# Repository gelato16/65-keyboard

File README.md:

# 65-keyboard
A 65% keyboard with fully custom parts designed using KiCAD and Solidworks. Made with a resin case, aluminum switch plate and soldered Epomaker silent keyswitches. 
This project is me introduction to Solidworks as someone preparing for a new robotics season, I'm not exactly a keyboard enthusiast (I might be becoming one) so I went with the essential 65% in order to keep things compact. 
features:
- 65% QWERTY layout
- Sandwich style assembly
- 7U spacebar
- Plate-mounted switches
- Custom PCB
- USB-C connection
- Custom switch plate

CAD photos:

PCB photos:

assembly guild: 
this is a sandwich style keyboard, meaning it is assembled in layers into a main base. The pcb slides easily into the main compartment followed by the switch plate, which the key switches click into. the keycaps and bezel finally lay on top and are screwed into place. 
Pictures of assembly design process below: 

Bill of materials:
https://docs.google.com/spreadsheets/d/1lCmeEfUbG34g1hUgpbVch2w63U2JIJnhS8jueZ3TIsw/edit?usp=sharing 
| Id        | Designator                                                                                                              | Footprint                           | Quantity                                                                                      | Designation                   | Link                                                                                          |
| :-------- | :---------------------------------------------------------------------------------------------------------------------- | :---------------------------------- | :-------------------------------------------------------------------------------------------- | :---------------------------- | :-------------------------------------------------------------------------------------------- |
| 1         | MX1-MX69                                                                                                                | SW_MX_HS_CPG151101S11_1u            | 69                                                                                            | MX_SW_HS                      | N/A                                                                                           |
| 2         | U1                                                                                                                      | LQFP-48_7x7mm_P0.5mm                | 1                                                                                             | STM32F072CBT6                 | https://www.digikey.ca/en/products/detail/stmicroelectronics/STM32F072CBT6/4815292            |
| 3         | C1, C3, C4, C5, C6                                                                                                      | C_1206_3126Metric                   | 7                                                                                             | 100nF                         | https://www.digikey.com/en/products/detail/kemet/C1206C104KARACTU/992167                      |
| 4         | C9, C10                                                                                                                 | C_1206_3126Metric                   | 2                                                                                             | 1uF                           | https://www.digikey.ca/en/products/detail/yageo/CC1206KKX7R7BB105/302915                      |
| 5         | R1 - R4                                                                                                                 | R_1206_3126Metric                   | 4                                                                                             | 5.1k                          | https://www.digikey.com/en/products/detail/stackpole-electronics-inc/RMCF1206FT5K10/1759499   |
| 6         | BOOT1, RST1                                                                                                             | SW_SPST_TL3342                      | 2                                                                                             | SW_SPST                       | https://jlcpcb.com/partdetail/ESwitch-TL3342F260QG/C2886894                                   |
| 7         | J1                                                                                                                      | USB_C_Receptacle_HRO_TYPE-C-31-M-12 | 1                                                                                             | USB_C_Receptacle_USB2.0       | https://jlcpcb.com/partdetail/C9900015525                                                     |
| 8         | F1                                                                                                                      | Fuse_1206_3216Metric                | 1                                                                                             | 500mA                         | https://www.lcsc.com/product-detail/C135341.html                                              |
| 9         | U5                                                                                                                      | C_0402_1005Metric                   | 1                                                                                             | TXB0101                       | https://www.lcsc.com/product-detail/C324081.html                                              |
| 10        | U3                                                                                                                      | SOT-23                              | 1                                                                                             | XC6206PxxxMR-Regulator_Linear | https://www.lcsc.com/product-detail/C5446.html                                                |
| 11        | D1-D69                                                                                                                  | D_SOD-123                           | 69                                                                                            | D_small                       | https://www.digikey.ca/en/products/detail/shenzhen-slkormicro-semicon-co-ltd/1N4148W/21853071 |
| 12        | U2                                                                                                                      | SOT-143                             | 1                                                                                             | PRTR5V0U2X                    | https://www.digikey.ca/en/products/detail/nexperia-usa-inc/PRTR5V0U2X-215/1163690             |
| 13        | C2                                                                                                                      | C_1206_3216Metric                   | 1                                                                                             | 10uF                          | https://www.digikey.ca/en/products/detail/kemet/C1206C106K8RACTU/1090842                      |
| 14        | C43, C44                                                                                                                | C_1206_3216Metric                   | 2                                                                                             | 0.1uF                         | https://www.digikey.ca/en/products/detail/tdk/C3216X7R2A104M160AA/513969                      |
| 15        | J2                                                                                                                      | PinHeader_1x05_P2.54mm_Vertical     | 1                                                                                             | Conn_01x05                    | https://www.digikey.ca/en/products/detail/harwin-inc/M20-9990546/3728232                      |
| 16        | J3                                                                                                                      | PinHeader_1x06_P2.54mm_Vertical     | 1                                                                                             | Conn_01x06                    | https://www.digikey.ca/en/products/detail/sullins-connector-solutions/PEC06SAFN/859339        |
|           |                                                                                                                         |                                     |                                                                                               |                               |                                                                                               |
| Physical: |                                                                                                                         |                                     |                                                                                               |                               |                                                                                               |
| Id        | Name                                                                                                                    | quantity                            | link                                                                                          |                               |                                                                                               |
| 1         | EPOMAKER Roseveil Silent Switch Set                                                                                     | 1                                   | https://epomaker.ca/products/epomaker-roseveil-silent-switch-set?_pos=3&_sid=4f9293093&_ss=r  |                               |                                                                                               |
| 2         | DUROCK Plate Mount Stabilizer V3                                                                                        | 1                                   | https://www.amazon.ca/dp/B0CTHT34MJ?ref=ppx_yo2ov_dt_b_fed_asin_title&th=1                    |                               |                                                                                               |
| 3         | dagaladoo Coffee Cat 140key keycaps,XDA Profile,dye Sublimation PBT Custom keycap with Key Puller for Gateron MX Switch | 1                                   | https://www.amazon.ca/dp/B0CF1ZS6D4?ref=ppx_yo2ov_dt_b_fed_asin_title&th=1                    |                               |                                                                                               |

All designs complete, assembly ongoing
(designed using Kicad, Solidworks and sketchbook)
(files with numbers ex:open2, are completed(not verified works.)

Known issues: None, 
Credits: My father for introducing me to all this. 
Sanity checked by my lovely best friend & my tech teacher

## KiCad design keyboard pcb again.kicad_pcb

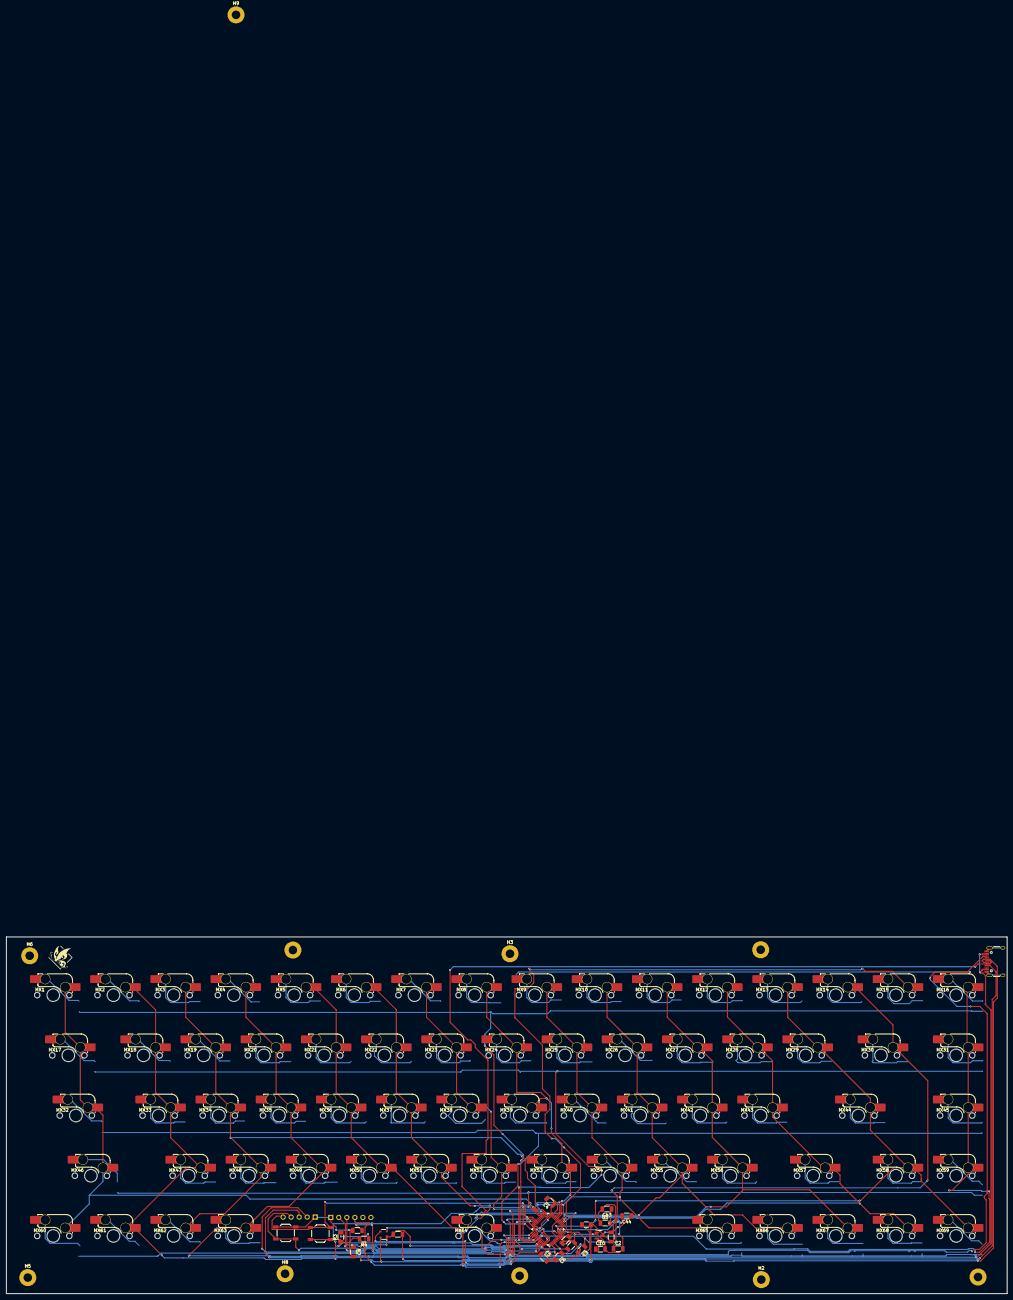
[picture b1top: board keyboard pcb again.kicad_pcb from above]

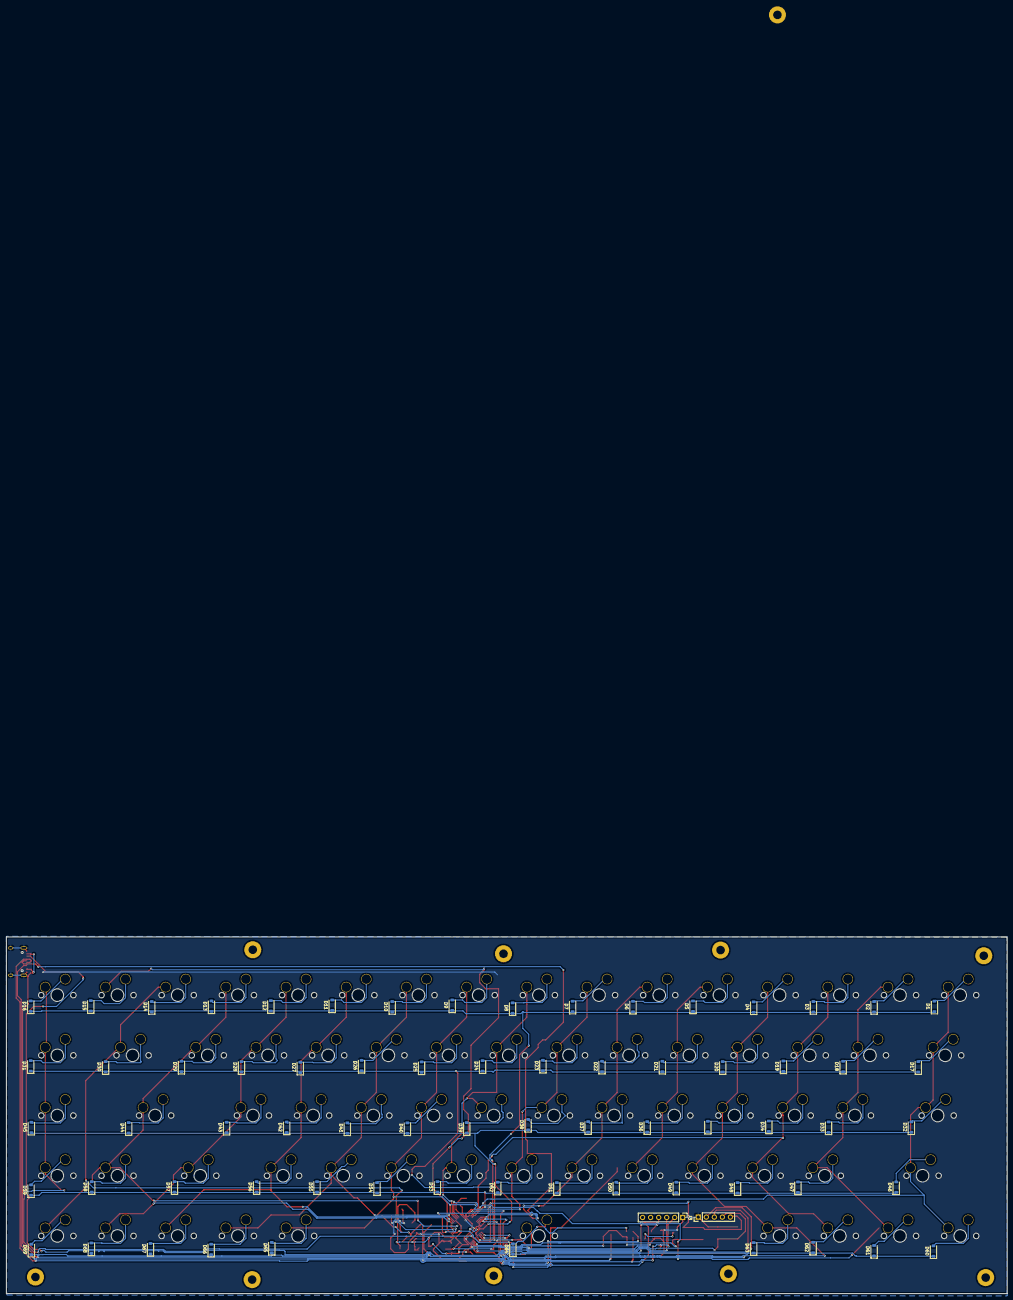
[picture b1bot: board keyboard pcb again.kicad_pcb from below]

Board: 2 copper layers, 316.7 x 112.9 mm, 175 parts (71 on the bottom side), 105 nets.

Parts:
 : LOGO; pic
BOOT1: SW_SPST; SW_SPST_TL3342
C1, C3, C4, C5, C6, C7, C8: 100nF; C_1206_3216Metric
C2: 10uF; C_1206_3216Metric
C9, C10: 1uF; C_1206_3216Metric
C43, C44: 0.1uF; C_1206_3216Metric
D1, D2, D3, D4, D5, D6, D7, D8, D9, D10, D11, D12, D13, D14, D15, D16, D17, D18, D19, D20, D21, D22, D23, D24, D25, D26, D27, D28, D29, D30, D31, D32, D33, D34, D35, D36, D37, D38, D39, D40, D41, D42, D43, D44, D45, D46, D47, D48, D49, D50, D51, D52, D53, D54, D55, D56, D57, D58, D59, D60, D61, D62, D63, D64, D65, D66, D67, D68, D69: D_Small; D_SOD-123
F1: 500mA; Fuse_1206_3216Metric
H1, H2, H3, H4, H5, H6, H7, H8, H9, H10: MountingHole; MountingHole_2.7mm_M2.5_Pad
J1: USB_C_Receptacle_USB2.0; USB_C_Receptacle_HRO_TYPE-C-31-M-12
J2: Conn_01x05; PinHeader_1x05_P2.54mm_Vertical
J3: Conn_01x04; PinHeader_1x06_P2.54mm_Vertical
MX1, MX2, MX3, MX4, MX5, MX6, MX7, MX8, MX9, MX10, MX11, MX12, MX13, MX14, MX15, MX16, MX17, MX18, MX19, MX20, MX21, MX22, MX23, MX24, MX25, MX26, MX27, MX28, MX29, MX30, MX31, MX32, MX33, MX34, MX35, MX36, MX37, MX38, MX39, MX40, MX41, MX42, MX43, MX44, MX45, MX46, MX47, MX48, MX49, MX50, MX51, MX52, MX53, MX54, MX55, MX56, MX57, MX58, MX59, MX60, MX61, MX62, MX63, MX64, MX65, MX66, MX67, MX68, MX69: MX_SW_HS; SW_MX_HS_CPG151101S11_1u
R1, R2, R3, R4: 5.1k; R_1206_3216Metric
RST1: SW_SPST; SW_SPST_TL3342
U1: STM32F072CBT6; LQFP-48_7x7mm_P0.5mm
U2: PRTR5V0U2X; SOT-143
U3: XC6206PxxxMR-Regulator_Linear; SOT-23
U5: TXB0101; C_1206_3216Metric

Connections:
+3V3: BOOT1.1 (A), C2.1, C3.1, C4.1, C5.1, C6.1, C7.1, C10.1, C43.2, J2.5, U1.1 (VBAT), U1.9 (VDDA), U1.24 (VDD), U1.36 (VDDIO2), U1.48 (VDD), U3.2 (VO), U5.1 (VCCA)
+5V: C8.1, C9.1, C44.1, F1.2, J3.2, U2.4 (VCC), U3.3 (VI)
BOOT0: BOOT1.2 (B), R3.1, U1.44 (BOOT0)
COL0: MX1.1, MX17.1, MX32.1, MX46.1, MX60.1, U1.28 (PB15)
COL1: MX2.1, MX18.1, MX33.1, MX47.1, MX61.1, U1.27 (PB14)
COL2: MX3.1, MX19.1, MX34.1, MX48.1, MX62.1, U1.26 (PB13)
COL3: MX4.1, MX20.1, MX35.1, MX49.1, MX63.1, U1.25 (PB12)
COL4: MX5.1, MX21.1, MX36.1, MX50.1, MX64.1, U1.10 (PA0)
COL5: MX6.1, MX22.1, MX37.1, MX51.1, U1.11 (PA1)
COL6: MX7.1, MX23.1, MX38.1, MX52.1, U1.21 (PB10)
COL7: MX8.1, MX24.1, MX39.1, MX53.1, U1.20 (PB2)
COL8: MX9.1, MX25.1, MX40.1, MX54.1, MX65.1, U1.19 (PB1)
COL9: MX10.1, MX26.1, MX41.1, MX55.1, MX66.1, U1.17 (PA7)
COL10: MX11.1, MX27.1, MX42.1, MX56.1, MX67.1, U1.16 (PA6)
COL11: MX12.1, MX28.1, MX43.1, MX57.1, MX68.1, U1.15 (PA5)
COL12: MX13.1, MX29.1, MX44.1, MX58.1, MX69.1, U1.14 (PA4)
COL13: MX14.1, MX30.1, U1.13 (PA3)
COL14: MX15.1, U1.12 (PA2)
COL15: MX16.1, MX31.1, MX45.1, MX59.1, U1.43 (PB7)
D+: J1.A6 (D+), J1.B6 (D+), U1.33 (PA12), U2.3 (I/O2)
D-: J1.A7 (D-), J1.B7 (D-), U1.32 (PA11), U2.2 (I/O1)
GND: C1.2, C2.2, C3.2, C4.2, C5.2, C6.2, C7.2, C8.2, C9.2, C10.2, C43.1, C44.2, J1.A1 (GND), J1.A12 (GND), J1.B1 (GND), J1.B12 (GND), J1.S1 (SHIELD), J2.1, J3.1, R1.1, R2.2, R4.2, RST1.2 (B), U1.8 (VSSA), U1.23 (VSS), U1.35 (VSS), U1.47 (VSS), U2.1 (GND), U3.1 (GND), U5.2 (GND)
NRST: C1.1, J2.4, RST1.1 (A), U1.2 (PC13), U1.3 (PC14), U1.4 (PC15), U1.5 (PF0), U1.6 (PF1), U1.7 (NRST), U1.18 (PB0)
unnamed: D1.2 (A), MX1.2
unnamed: D2.2 (A), MX2.2
unnamed: D3.2 (A), MX3.2
unnamed: D4.2 (A), MX4.2
unnamed: D5.2 (A), MX5.2
unnamed: D6.2 (A), MX6.2
unnamed: D7.2 (A), MX7.2
unnamed: D8.2 (A), MX8.2
unnamed: D9.2 (A), MX9.2
unnamed: D10.2 (A), MX10.2
unnamed: D11.2 (A), MX11.2
unnamed: D12.2 (A), MX12.2
unnamed: D13.2 (A), MX13.2
unnamed: D14.2 (A), MX14.2
unnamed: D15.2 (A), MX15.2
unnamed: D16.2 (A), MX16.2
unnamed: D17.2 (A), MX17.2
unnamed: D18.2 (A), MX18.2
unnamed: D19.2 (A), MX19.2
unnamed: D20.2 (A), MX20.2
unnamed: D21.2 (A), MX21.2
unnamed: D22.2 (A), MX22.2
unnamed: D23.2 (A), MX23.2
unnamed: D24.2 (A), MX24.2
unnamed: D25.2 (A), MX25.2
unnamed: D26.2 (A), MX26.2
unnamed: D27.2 (A), MX27.2
unnamed: D28.2 (A), MX28.2
unnamed: D29.2 (A), MX29.2
unnamed: D30.2 (A), MX30.2
unnamed: D31.2 (A), MX31.2
unnamed: D32.2 (A), MX32.2
unnamed: D33.2 (A), MX33.2
unnamed: D34.2 (A), MX34.2
unnamed: D35.2 (A), MX35.2
unnamed: D36.2 (A), MX36.2
unnamed: D37.2 (A), MX37.2
unnamed: D38.2 (A), MX38.2
unnamed: D39.2 (A), MX39.2
unnamed: D40.2 (A), MX40.2
unnamed: D41.2 (A), MX41.2
unnamed: D42.2 (A), MX42.2
unnamed: D43.2 (A), MX43.2
unnamed: D44.2 (A), MX44.2
unnamed: D45.2 (A), MX45.2
unnamed: D46.2 (A), MX46.2
unnamed: D47.2 (A), MX47.2
unnamed: D48.2 (A), MX48.2
unnamed: D49.2 (A), MX49.2
unnamed: D50.2 (A), MX50.2
unnamed: D51.2 (A), MX51.2
unnamed: D52.2 (A), MX52.2
unnamed: D53.2 (A), MX53.2
unnamed: D54.2 (A), MX54.2
unnamed: D55.2 (A), MX55.2
unnamed: D56.2 (A), MX56.2
unnamed: D57.2 (A), MX57.2
unnamed: D58.2 (A), MX58.2
unnamed: D59.2 (A), MX59.2
unnamed: D60.2 (A), MX60.2
unnamed: D61.2 (A), MX61.2
unnamed: D62.2 (A), MX62.2
unnamed: D63.2 (A), MX63.2
unnamed: D64.2 (A), MX64.2
unnamed: D65.2 (A), MX65.2
unnamed: D66.2 (A), MX66.2
unnamed: D67.2 (A), MX67.2
unnamed: D68.2 (A), MX68.2
unnamed: D69.2 (A), MX69.2
unnamed: J1.A5 (CC1), R1.2
unnamed: J1.B5 (CC2), R2.1
unnamed: R3.2, R4.1
ROW0: D1.1 (K), D2.1 (K), D3.1 (K), D4.1 (K), D5.1 (K), D6.1 (K), D7.1 (K), D8.1 (K), D9.1 (K), D10.1 (K), D11.1 (K), D12.1 (K), D13.1 (K), D14.1 (K), D15.1 (K), D16.1 (K), U1.42 (PB6)
ROW1: D17.1 (K), D18.1 (K), D19.1 (K), D20.1 (K), D21.1 (K), D22.1 (K), D23.1 (K), D24.1 (K), D25.1 (K), D26.1 (K), D27.1 (K), D28.1 (K), D29.1 (K), D30.1 (K), D31.1 (K), U1.41 (PB5)
ROW2: D32.1 (K), D33.1 (K), D34.1 (K), D35.1 (K), D36.1 (K), D37.1 (K), D38.1 (K), D39.1 (K), D40.1 (K), D41.1 (K), D42.1 (K), D43.1 (K), D44.1 (K), D45.1 (K), U1.40 (PB4)
ROW3: D46.1 (K), D47.1 (K), D48.1 (K), D49.1 (K), D50.1 (K), D51.1 (K), D52.1 (K), D53.1 (K), D54.1 (K), D55.1 (K), D56.1 (K), D57.1 (K), D58.1 (K), D59.1 (K), U1.39 (PB3)
ROW4: D60.1 (K), D61.1 (K), D62.1 (K), D63.1 (K), D64.1 (K), D65.1 (K), D66.1 (K), D67.1 (K), D68.1 (K), D69.1 (K), U1.38 (PA15)
SCL: J3.3, U1.45 (PB8)
SDA: J3.4, U1.46 (PB9)
SWCLK: J2.2, U1.37 (PA14)
SWD: J2.3, U1.34 (PA13)
VBUS: F1.1, J1.A4 (VBUS), J1.A9 (VBUS), J1.B4 (VBUS), J1.B9 (VBUS)

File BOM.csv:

"Id";"Designator";"Footprint";"Quantity";"Designation";"Supplier and ref";
1;"MX45,MX32,MX1,MX42,MX51,MX24,MX18,MX21,MX25,MX48,MX3,MX12,MX33,MX31,MX10,MX11,MX67,MX59,MX29,MX41,MX39,MX30,MX40,MX9,MX34,MX50,MX37,MX61,MX2,MX64,MX13,MX4,MX47,MX6,MX66,MX28,MX57,MX65,MX63,MX62,MX8,MX60,MX36,MX54,MX38,MX53,MX46,MX5,MX55,MX23,MX43,MX56,MX58,MX16,MX17,MX26,MX14,MX52,MX44,MX20,MX15,MX68,MX19,MX22,MX35,MX69,MX7,MX49,MX27";"SW_MX_1u";69;"MX_SW_solder";;;
2;"U1";"LQFP-48_7x7mm_P0.5mm";1;"STM32F072CBT6";;; https://www.digikey.ca/en/products/detail/stmicroelectronics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
3;"C6,C3,C4,C5,C7,C8,C1";"C_0402_1005Metric";7;"100nF";;; https://www.lcsc.com/product-detail/C307331.html
4;"C9,C10";"C_0402_1005Metric";2;"1uF";;; https://www.lcsc.com/product-detail/C307331.html
5;"R2,R3,R1,R4";"R_0402_1005Metric";4;"5.1k";;; https://www.lcsc.com/product-detail/C25905.html
6;"BOOT1,RST1";"SW_SPST_TL3342";2;"SW_SPST";;; https://jlcpcb.com/partdetail/ESwitch-TL3342F260QG/C2886894
7;"J1";"USB_C_Receptacle_HRO_TYPE-C-31-M-12";1;"USB_C_Receptacle_USB2.0";;; https://jlcpcb.com/partdetail/C9900015525
8;"F1";"Fuse_1206_3216Metric";1;"500mA";;; https://www.lcsc.com/product-detail/C135341.html
9;"U5";"C_0402_1005Metric";1;"TXB0101";;; https://www.lcsc.com/product-detail/C324081.html
10;"U3";"SOT-23";1;"XC6206PxxxMR-Regulator_Linear";;; https://www.lcsc.com/product-detail/C5446.html
11;"U2";"SOT-143";1;"PRTR5V0U2X";;;  https://www.lcsc.com/product-detail/C2827688.html
12;"C2";"C_0402_1005Metric";1;"10uF";;; https://www.lcsc.com/product-detail/C307331.html
13;"C43,C44";"C_0402_1005Metric";2;"0.1uF";;; https://www.lcsc.com/product-detail/C307331.html
14;"D59,D69,D54,D44,D41,D47,D5,D23,D46,D38,D27,D9,D31,D24,D65,D55,D60,D34,D21,D68,D62,D26,D32,D48,D25,D20,D61,D42,D22,D43,D16,D56,D3,D1,D45,D19,D7,D35,D67,D40,D64,D33,D37,D63,D39,D66,D58,D49,D8,D12,D53,D11,D6,D52,D2,D15,D36,D57,D17,D51,D14,D18,D30,D50,D13,D4,D28,D29,D10";"D_SOD-123";69;"D_Small";;; https://www.digikey.ca/en/products/detail/shenzhen-slkormicr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
15;"J2";"PinHeader_1x05_P2.54mm_Vertical";1;"Conn_01x05";;; 
16;"J3";"PinHeader_1x04_P2.54mm_Vertical";1;"Conn_01x04";;; 

physical:
EPOMAKER Roseveil Silent Switch Set https://epomaker.ca/products/epomaker-roseveil-silent-switch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 
DUROCK Plate Mount Stabilizer V3, Innovative Pre-Clipped Stem for Minimum Wire Wobble 2U 6.25U 7U Keyboard Stabilizers https://www.amazon.ca/dp/B0CTHT34MJ?ref=ppx_yo2ov_dt_b_fed_a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
dagaladoo Coffee Cat 140key keycaps,XDA Profile,dye Sublimation PBT Custom keycap with Key Puller for Gateron MX Switch Mechanical Gaming https://www.amazon.ca/dp/B0CF1ZS6D4?ref=ppx_yo2ov_dt_b_fed_a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
